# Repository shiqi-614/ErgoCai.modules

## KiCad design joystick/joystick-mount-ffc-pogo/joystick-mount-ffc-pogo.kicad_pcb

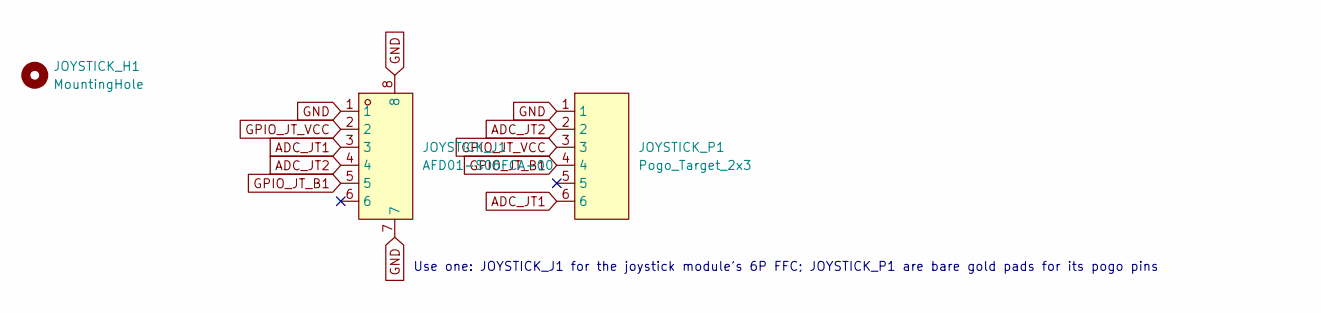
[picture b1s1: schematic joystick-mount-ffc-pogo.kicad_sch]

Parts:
JOYSTICK_H1: MountingHole; Ps4JoystickMount_FfcPogo
JOYSTICK_J1: AFD01-S06FCA-00; FPC-SMD_6P-P0.50_JS_AFD01-S06FCA-00; LCSC Part C18198574
JOYSTICK_P1: Pogo_Target_2x3; Pogo_Target_2x3_P2.54x3.50mm

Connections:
ADC_JT1: JOYSTICK_J1.3, JOYSTICK_P1.6
ADC_JT2: JOYSTICK_J1.4, JOYSTICK_P1.2
GND: JOYSTICK_J1.1, JOYSTICK_J1.7, JOYSTICK_J1.8, JOYSTICK_P1.1
GPIO_JT_B1: JOYSTICK_J1.5, JOYSTICK_P1.4
GPIO_JT_VCC: JOYSTICK_J1.2, JOYSTICK_P1.3

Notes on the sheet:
Use one: JOYSTICK_J1 for the joystick module's 6P FFC; JOYSTICK_P1 are bare gold pads for its pogo pins

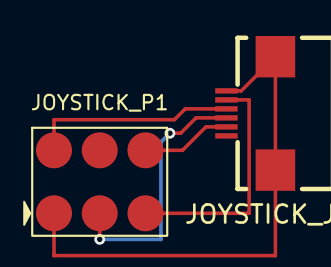
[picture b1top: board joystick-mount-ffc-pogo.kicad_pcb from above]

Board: 2 copper layers, 3 parts (0 on the bottom side), 5 nets.

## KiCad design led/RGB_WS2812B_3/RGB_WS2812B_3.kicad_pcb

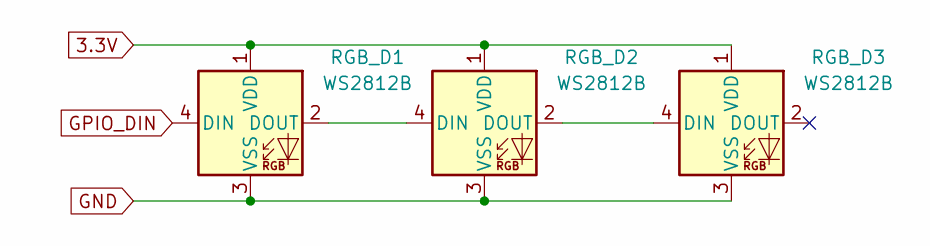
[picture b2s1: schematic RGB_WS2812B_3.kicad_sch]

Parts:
RGB_D1, RGB_D2, RGB_D3: WS2812B; LED_WS2812B_PLCC4_5.0x5.0mm_P3.2mm

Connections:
3.3V: RGB_D1.1 (VDD), RGB_D2.1 (VDD), RGB_D3.1 (VDD)
GND: RGB_D1.3 (VSS), RGB_D2.3 (VSS), RGB_D3.3 (VSS)
GPIO_DIN: RGB_D1.4 (DIN)
unnamed: RGB_D1.2 (DOUT), RGB_D2.4 (DIN)
unnamed: RGB_D2.2 (DOUT), RGB_D3.4 (DIN)

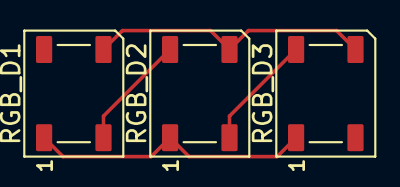
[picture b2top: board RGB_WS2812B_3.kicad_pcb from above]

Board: 2 copper layers, 3 parts (0 on the bottom side), 4 nets.
